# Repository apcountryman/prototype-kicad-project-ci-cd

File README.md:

# prototype-kicad-project-ci-cd

KiCad project GitHub Actions CI/CD prototype.

*NOTE: The test printed circuit board contained within this repository was developed
specifically to test the CI/CD pipeline, and does not have the finishing touches expected
of a finished product*

## Obtaining the Source Code
HTTPS:
```shell
git clone --recurse-submodules https://github.com/apcountryman/prototype-kicad-project-ci-cd.git
```
SSH:
```shell
git clone --recurse-submodules git@github.com:apcountryman/prototype-kicad-project-ci-cd.git
```

## Usage
This repository's Git `pre-commit` hook script is the simplest way to test this project
during development.
See the `pre-commit` script's help text for usage details.
```shell
./git/hooks/pre-commit --help
```

Additional checks, such as static analysis, are performed by this project's GitHub Actions
CI workflow.

## Versioning
`prototype-kicad-project-ci-cd` follows the [Abseil Live at Head
philosophy](https://abseil.io/about/philosophy).

## Workflow
`prototype-kicad-project-ci-cd` uses the [GitHub
flow](https://guides.github.com/introduction/flow/) workflow.

## Git Hooks
To install this repository's Git hooks, execute the `install` script located in the
`git/hooks` directory.
See the `install` script's help text for usage details.
```shell
./git/hooks/install --help
```

## Code of Conduct
`prototype-kicad-project-ci-cd` has adopted the Contributor Covenant 2.0 code of conduct.
For more information, [see the `CODE_OF_CONDUCT.md` file in this
repository](CODE_OF_CONDUCT.md).

## Contributing
If you are interested in contributing to `prototype-kicad-project-ci-cd`, please [read the
`CONTRIBUTING.md` file in this repository](CONTRIBUTING.md).

## Authors
- Andrew Countryman
- Jay Lamb

## License
`prototype-kicad-project-ci-cd` is licensed under the CERN Open Hardware License Version
2 - Permissive (CERN-OHL-P v2).
For more information, [see the `LICENSE` file in this repository](LICENSE).
Additional information can be found in the Guide to the CERN-OHL-P v2 which is available
in both [ODT](LICENSE-guide.odt) and [PDF](LICENSE-guide.pdf) formats.

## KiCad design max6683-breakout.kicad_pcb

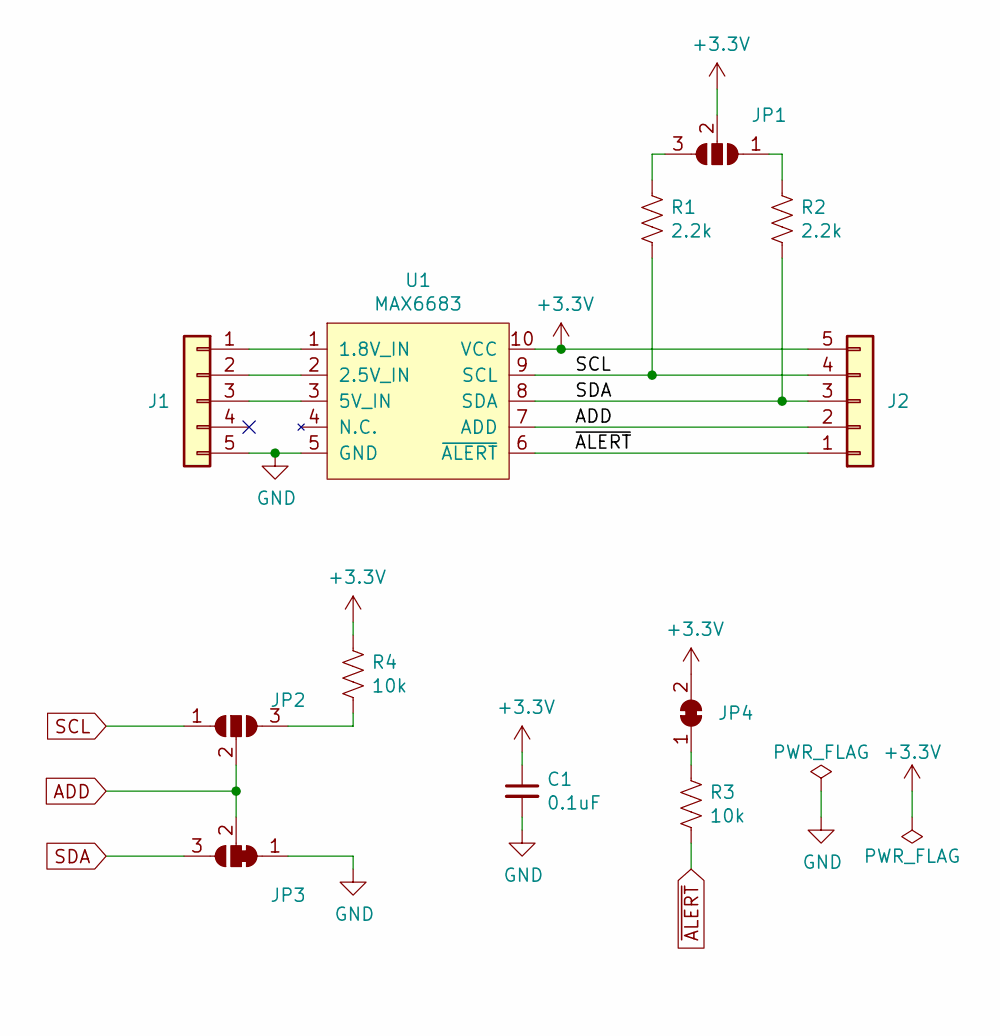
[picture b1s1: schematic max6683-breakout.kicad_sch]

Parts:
C1: 0.1uF; R_0805_2012Metric; Part Number CC0805KRX7R9BB104
J1, J2: Conn_01x05; PinHeader_1x05_P2.54mm_Vertical
JP1, JP2: SolderJumper_3_Open; SolderJumper-3_P1.3mm_Open_RoundedPad1.0x1.5mm
JP3: (no value)
JP4: SolderJumper_2_Bridged; SolderJumper-2_P1.3mm_Bridged_RoundedPad1.0x1.5mm
R1, R2: 2.2k; R_0603_1608Metric; Part Number ERJ-3EKF2201V
R3, R4: 10k; R_0603_1608Metric; Part Number ERJ-3EKF1002V
U1: MAX6683; MSOP-10_3x3mm_P0.5mm; Part Number MAX6683AUB

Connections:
+3V3: C1.1, J2.5, JP1.2 (C), JP4.2 (B), R4.1, U1.10 (VCC)
ADD: J2.2, JP2.2 (C), JP3.2 (C), U1.7 (ADD)
GND: C1.2, J1.5, JP3.1 (A), U1.5 (GND)
unnamed: J1.1, U1.1 (1.8V_IN)
unnamed: J1.2, U1.2 (2.5V_IN)
unnamed: J1.3, U1.3 (5V_IN)
unnamed: JP1.1 (A), R2.1
unnamed: JP1.3 (B), R1.1
unnamed: JP2.3 (B), R4.2
unnamed: JP4.1 (A), R3.1
SCL: J2.4, JP2.1 (A), R1.2, U1.9 (SCL)
SDA: J2.3, JP3.3 (B), R2.2, U1.8 (SDA)
~ALERT: J2.1, R3.2, U1.6 (~ALERT)

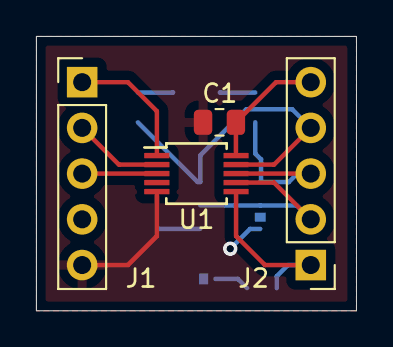
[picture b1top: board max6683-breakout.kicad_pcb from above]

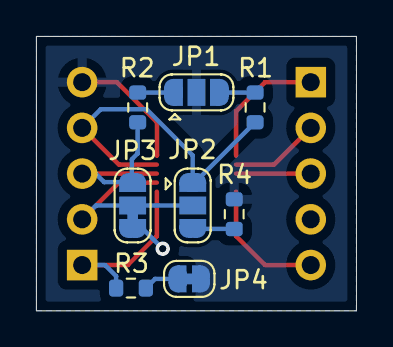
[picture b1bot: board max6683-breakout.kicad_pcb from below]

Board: 2 copper layers, 17.8 x 15.2 mm, 12 parts (8 on the bottom side), 13 nets.

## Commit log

2021-08-03 Fix README License section formatting
    Resolves #3 (Fix README License section formatting).
2021-08-03 Fix README License section formatting (#4)
    Resolves #3 (Fix README License section formatting).
2021-08-09 Alphabetize script argument parsing
    Resolves #5 (Alphabetize script argument parsing).
2021-08-09 Alphabetize script argument parsing (#6)
    Resolves #5 (Alphabetize script argument parsing).
2021-09-02 Add KiAuto repository as a project submodule
    Supports #2.
2021-09-02 Add electrical rules compliance check ci job
    Supports #2.
2021-09-02 Apply suggestions from code review
    Fix formatting
    Supports #2.
2021-09-02 Apply suggestions from code review
    Fix syntax issues
    Supports #2.
2021-09-02 Add electrical rules compliance ci job (#7)
    Resolves #2 (Add electrical rules compliance CI job).
2021-09-07 Add design rules compliance CI job
    Supports #9.
2021-09-07 Remove unecessary function from script
    Bad copy/paste.
2021-09-07 Update formatting
    Update formatting per peer review comments.
    Supports #9.
2021-09-07 Fix CI script
    Make ignore_unconnected_nets variable read only after argument parsing.
2021-09-07 Revert "Remove unecessary function from script"
    This reverts commit 11ed1a15c8215b550d0beee5bad7c713d071cba2.
    Supports #9.
2021-09-08 Add design rules compliance CI job (#10)
    Resolves #9 (Add design rules compliance CI job).
2021-09-13 Remove unused function
    Resolves #11 (Remove unused function).
2021-09-13 Remove unused function (#12)
    Resolves #11 (Remove unused function).
2021-09-15 Add Jay Lamb to authors list
2021-09-15 Add Jay Lamb to authors list (#14)
2021-09-20 Add schematic pdf generation CI script to project
    Supports #15.
2021-09-20 Add schematic PDF generation script execution to project workflow
    Supports #15.
2021-09-20 Apply suggestions from code review
    Update formatting per peer review comments.
    Supports #15.
2021-09-20 Add schematic PDF(s) generation CI job (#16)
    Resolves #15 (Add schematic PDF(s) generation CI job).
2021-09-20 Fix CI scripts description indentation
    Supports #17.
2021-09-20 Fix CI scripts description indentation (#18)
    Resolves #17 (Fix CI scripts description indentation).
2021-09-25 Add traditional BOM generation to project
    Supports #20.
2021-09-26 Apply suggestions from code review
    Correct indentation per peer suggestion.
    Supports #20.
2021-09-27 Update CI job to avoid shellcheck error SC2155
    Supports #20.
2021-09-27 Apply suggestions from code review
    Place variable declaration and assignment on same line for consistency.
    Supports #20.
2021-09-27 Add traditional BOM(s) generation CI job (#21)
    Resolves #20 (Add traditional BOM(s) generation CI job).
2021-10-09 Add InteractiveHtmlBom project as submodule
    Supports #23.
2021-10-09 Add interactive BOM generation CI script
    Supports #23.
2021-10-09 Add interactive BOM(s) generation (and archiving) CI job
    Supports #23.
2021-10-09 Add interactive BOM(s) generation CI job (#24)
    Resolves #23 (Add interactive BOM(s) generation CI job).
2021-10-21 Add KiBot as a project submodule
    Supports #26.
2021-10-21 Add production files generation CI script
    Supports #26.
2021-10-21 Add production file generation to ci workflow
    Supports #26.
2021-10-21 Add KiBot configuration to project
    Supports #26.
2021-10-22 Fix traditional BOM generation CI script XML BOM identification logic
    Resolves #28 (Fix traditional BOM generation CI script XML BOM
    identification logic).
    The traditional BOM generation CI script did not restrict its search for
    XML BOMs to the directory where generated XML BOMs are placed. This
    could result in other XML files being misidentified as XML BOMs.
2021-10-22 Fix traditional BOM generation CI script XML BOM identification logic (#29)
    Resolves #28 (Fix traditional BOM generation CI script XML BOM
    identification logic).
    The traditional BOM generation CI script did not restrict its search for
    XML BOMs to the directory where generated XML BOMs are placed. This
    could result in other XML files being misidentified as XML BOMs.
2021-10-22 Add production files generation CI job (#27)
    Resolves #26 (Add production files generation CI job).
2021-10-23 Improve CI scripts help text
    Resolves #30 (Improve CI scripts help text).
2021-10-23 Improve CI scripts help text (#32)
    Resolves #30 (Improve CI scripts help text).
2021-11-11 Add PcbDraw as a project submodule
    Supports #34.
2021-11-11 Add render generation CI script to project.
    Supports #34.
2021-11-11 Add PCB render CI job to workflow
    Supports #34.
2021-11-11 Add PCB renders generation CI job (#35)
    Resolves #34 (Add PCB renders generation CI job)
2021-11-11 Update libraries
    Resolves #36 (Update libraries).
2021-11-11 Update libraries (#37)
    Resolves #36 (Update libraries).
2021-11-11 Update utilities
    Resolves #38 (Update utilities).
2021-11-11 Update utilities (#39)
    Resolves #38 (Update utilities).
2021-12-04 Refactor deliverable generation CI scripts/jobs to assume the repository has a specific structure
    Resolves #40 (Refactor deliverable generation CI scripts/jobs to assume
    the repository has a specific structure).
2021-12-04 Fix CI script inconsistencies
    Supports #40.
2021-12-04 Fix PCB render file names
    Supports #40.
2021-12-06 Refactor deliverable generation CI scripts/jobs to assume the repository has a specific structure (#41)
    Resolves #40 (Refactor deliverable generation CI scripts/jobs to assume
    the repository has a specific structure).
2022-01-19 Add MAX6683 breakout project
    Project currently contains blank schematic (.sch) and layout (.kicad_pcb).
    Supports #43.
2022-01-23 Remove unnecessary information from KiCad project file.
    Supports #44.
2022-01-23 Add Python dependencies to CI configuration
    Supports #44.
2022-01-23 Add additional Python dependencies to CI configuration
    Supports #44.
2022-01-23 More Python CI job dependencies
    Supports #44.
2022-01-24 Remove redundant call to 'run'
    Supports #44.
2022-01-24 Add python3-wand dependency
    Supports #44.
2022-01-24 Update dependency to WX
    Supports #44.
2022-01-24 Update interactive BOM CI job dependencies
    Supports #44.
2022-01-24 Update dependencies for interactive BOM CI job
    Supports #44.
2022-02-06 Update gitignore
    Supports #44.
2022-02-06 Add MAX6683 schematic symbol to project
    Supports #44.
2022-02-07 Add parts to schematic
    Supports #44.
2022-02-13 Correct ci pipeline issues per peer suggestions
    Replaced an isntance of apt-get with an instance of apt.
    Added apt update command prior to each apt install command.
    Supports #44.
2022-02-13 Add Kicad installation to ci jobs
    Supports #44.
2022-02-13 Annotate schematic
    Supports #44.
2022-02-13 Add generated netlist
    Supports #44.
2022-02-13 Import netlist into pcbnew
    Supports #44.
2022-02-13 Fix CI job KiCad project name identification
    Resolves #45 (Fix CI job KiCad project name identification).
2022-02-13 Fix CI job KiCad project name identification (#46)
    Resolves #45 (Fix CI job KiCad project name identification).
2022-03-29 Transition to KiCad 6
    Resolves #47 (Transition to KiCad 6).
2022-03-29 Transition to KiCad 6 (#48)
    Resolves #47 (Transition to KiCad 6).
2022-04-14 Transition project to KiCad 6
    Supports #44.
2022-04-14 Test updated ci run command
    Supports #74.
2022-04-14 Another test
    Supports #74.
2022-04-14 Update CI pipeline (ERC)
    Supports #44.
2022-04-14 Add xdotool install to ERC CI job
    Supports #44.
2022-04-14 Connect schematic nets
    Supports #44.
2022-04-19 Update I2C pullup resistor value
    Supports #44.
2022-04-19 Remove solder jumpers and power flags from BOM
    Supports #44.
2022-04-19 Connect device address pin to GND
    Supports #44.
2022-04-19 Add NC solder jumper to ALERT net
    Supports #44.
2022-05-20 Remove depricated files from project
    Supports #44.
2022-05-20 Move test PCB files into project root
    Supports #44.
2022-05-21 Initial PCB component placement
    Supports #44.
2022-05-22 Update PcbDraw submodule
    Supports #44.
2022-05-22 Fix CI scripts for KiCad 6 compatibility
    Resolves #49 (Fix CI scripts for KiCad 6 compatibility).
2022-05-22 Fix CI scripts for KiCad 6 compatibility (#50)
    Resolves #49 (Fix CI scripts for KiCad 6 compatibility).
2022-05-22 Update CI job dependencies
    Supports #44.
2022-05-22 More CI job dependencies
    Supports #44.
2022-05-23 Remove unconnected net ignore flag for DRC
    Supports #44.
2022-05-23 Fix check-design-rules-compliance CI script --ignore-unconnected-nets option handling
    Resolves #51 (Fix check-design-rules-compliance CI script
    --ignore-unconnected-nets option handling).
2022-05-23 Fix check-design-rules-compliance CI script --ignore-unconnected-nets option handling (#52)
    Resolves #51 (Fix check-design-rules-compliance CI script
    --ignore-unconnected-nets option handling).
2022-05-23 Add dependencies to DRC CI job
    Supports #44.
2022-05-25 Update interactive BOM script to support headless environment
    Supports #44.
2022-05-27 Add PCB outline
    Parts moved for clearance and ease of routing.
    Supports #44.
2022-05-27 Update PCB to eliminate clearance DRC issues
    Supports #44.
2022-05-27 Begin routing
    Supports #44.
2022-05-30 Complete routing
    Supports #44.
2022-06-05 Update ci workflow per peer suggestion
    Supports #44.
2022-06-05 Remove swap files from .gitignore
    Supports #44.
2022-06-05 Remove netlist from tracked files
    Supports #44.
2022-06-05 Inject ERC errors to test CI job
    Supports #44.
2022-06-05 Remove intentional ERC errors
    Supports #44.
2022-06-06 Update Maxim library to use KiCad 6 file format
    Supports #44.
2022-06-06 Update README
    Supports #44.
2022-06-06 Add test printed circuit board project (#44)
    Resolves #43 (Add test printed circuit board project).
2022-06-15 Add release generation
    Resolves #53 (Add release generation).
2022-06-15 Add release generation (#54)
    Resolves #53 (Add release generation).
